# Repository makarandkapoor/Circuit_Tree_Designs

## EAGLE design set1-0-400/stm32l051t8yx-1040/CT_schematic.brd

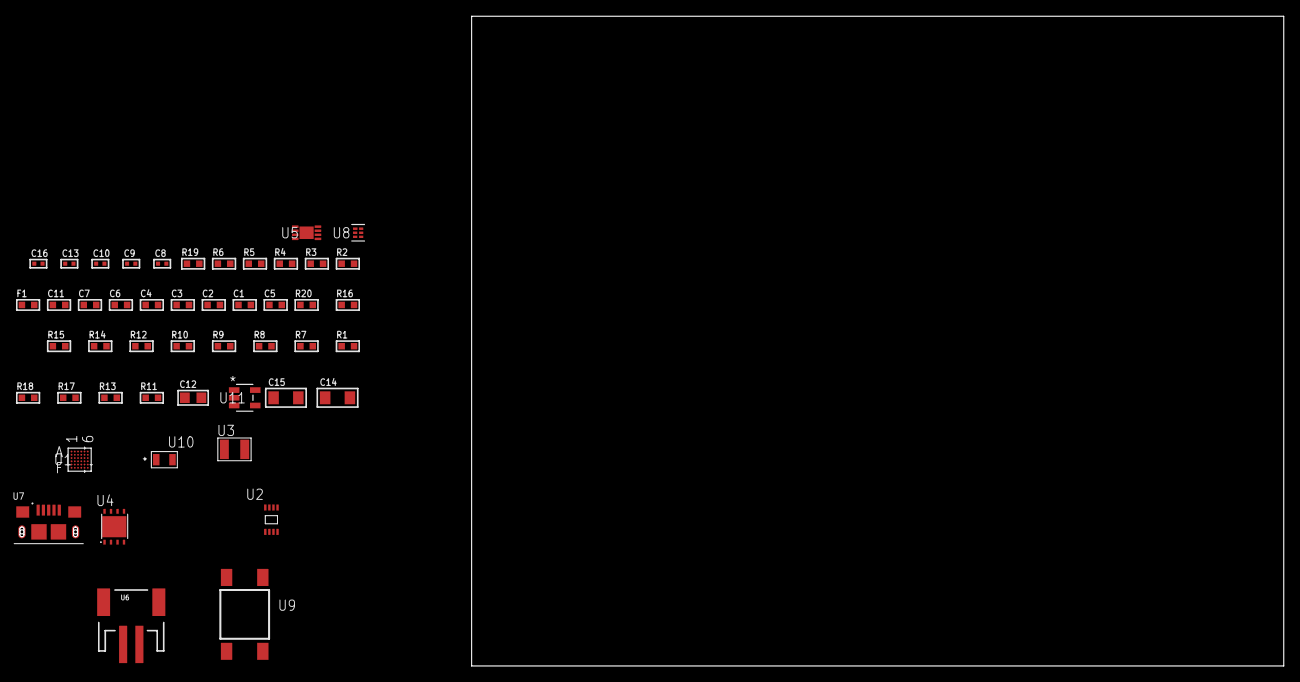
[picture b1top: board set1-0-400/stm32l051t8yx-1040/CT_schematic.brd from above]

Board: 2 copper layers, 155.6 x 80.0 mm, 48 parts (0 on the bottom side), 24 nets, no tracks yet.

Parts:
C1, C2, C3, C4: 1e-07; C0603
C5: 4.7e-06; C0603
C6: 1e-08; C0603
C7, C11: 1e-06; C0603
C8, C9: 1e-11; C0402
C10, C16: 1e-08; C0402
C12: 1e-05; C0805
C13: 1e-07; C0402
C14, C15: 1e-05; C1206
F1: 240.0; L0603
R1, R7, R8, R9, R10, R14, R15, R20: 10000.0; R0603
R2: 1000.0; R0603
R3: 910.0; R0603
R4: 4700.0; R0603
R5, R6: 2200.0; R0603
R11, R13: 100000.0; R0603
R12: 36000.0; R0603
R16: 82000.0; R0603
R17: 300000.0; R0603
R18: 120000.0; R0603
R19: 2000.0; R0603
U1: STM32L051T8Y6; WLCSP36
U2: 24AA32AT-I/MNY; TDFN-8/6MM
U3: ABS07-32.768KHZ-7-T
U4: LP2951ACSDX/NOPB; WSON-8
U5: MCP73831T-2ACI/MC; DFN8_2X3MC
U6: S2B-PH-SM4-TB(LF)(SN); JST-2-SMD
U7: 10118193-0001LF; FCI_10118193-0001LF
U8: TPS3895ADRYR; SON-6
U9: 4-1437565-2; SW_4-1437565-2
U10: Q65110A2395; LGM67K-G1J2-24-Z
U11: nc7sz125m5x; NC7SZ125M5X

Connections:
CLK_CRYSTAL_U1_A6: C8.1, U1.A6, U3.1
CLK_CRYSTAL_U1_B6: C9.1, U1.B6, U3.2
GND: C1.2, C2.2, C3.2, C4.2, C5.2, C6.2, C7.2, C8.2, C9.2, C10.2, C11.2, C12.2, C13.2, C14.2, C15.2, C16.2, R2.2, R7.2, R10.2, R13.2, R16.2, R18.2, R19.2, U1.D6, U2.4, U2.7, U4.3, U4.4, U4.PAD, U5.6, U5.9, U6.2, U7.5, U7.6, U7.7, U7.8, U7.9, U8.2, U10.C, U11.1, U11.3
INPUT_USBPOWER_5V: C14.1, R20.2, U5.1, U5.2, U7.1
NET_U1_A4: R6.1, U1.A4, U2.5
NET_U1_B4: R5.1, U1.B4, U2.6
NET_U1_C5: R7.1, U1.C5
NET_U1_C6: R4.1, U1.C6, U11.4
NET_U1_D5: C6.1, C7.1, F1.1, U1.D5, U1.E6
NET_U1_F5: R3.1, U1.F5, U10.A
NET_U1_F6: R1.1, U1.F6, U9.3, U9.4
NET_U2_1: R8.1, U2.1
NET_U2_2: R9.1, U2.2
NET_U2_3: R10.1, U2.3
NET_U4_5: R11.1, U4.5
NET_U4_7: R12.2, R13.1, U4.7
NET_U5_5: R20.1, U5.5
NET_U5_8: R19.1, U5.8
NET_U8_1: R15.1, R16.1, U8.1
NET_U8_3: R17.2, R18.1, U8.3
NET_U8_4: R14.1, U8.4, U11.2
NET_U9_1: R2.1, U9.1, U9.2
VCC_S1_3V7: C11.1, C15.1, U4.8, U5.3, U5.4, U6.1
VCC_TIER1_1V8: C1.1, C2.1, C3.1, C4.1, C5.1, C10.1, C12.1, C13.1, C16.1, F1.2, R1.2, R3.2, R4.2, R5.2, R6.2, R8.2, R9.2, R11.2, R12.1, R14.2, R15.2, R17.1, U1.A5, U1.F1, U2.8, U4.1, U8.6, U11.5

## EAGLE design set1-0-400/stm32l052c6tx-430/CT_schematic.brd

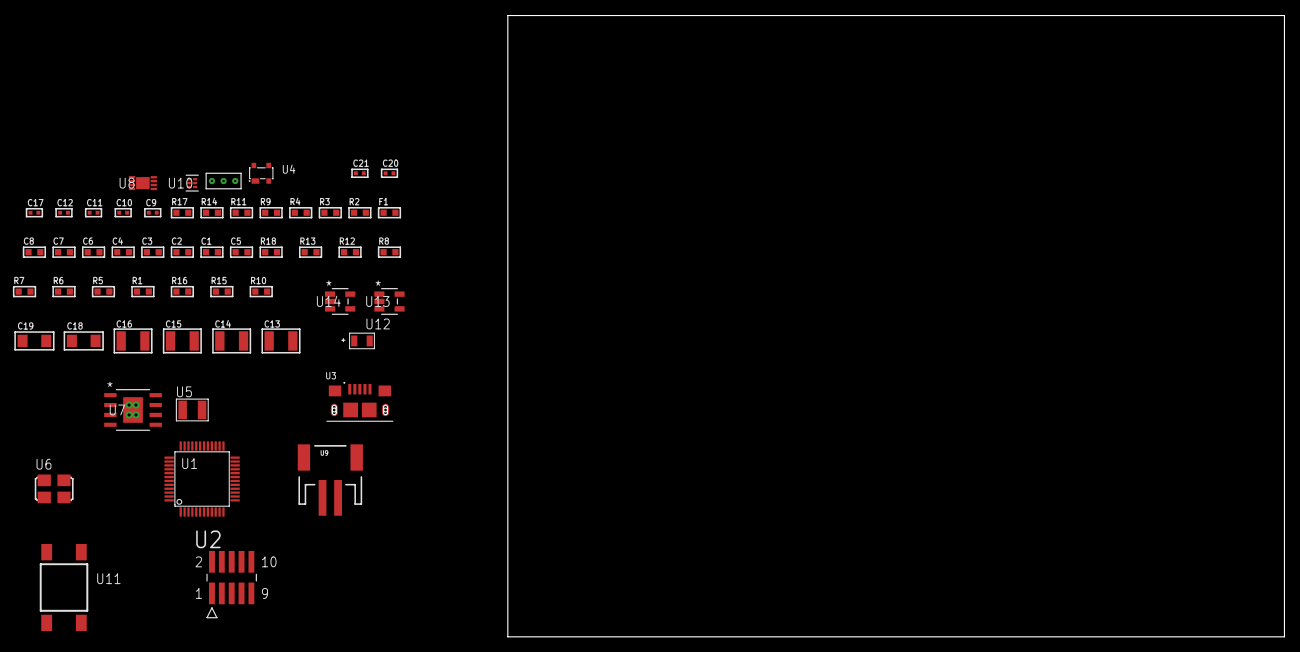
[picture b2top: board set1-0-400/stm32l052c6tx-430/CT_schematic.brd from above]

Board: 2 copper layers, 122.6 x 80.0 mm, 55 parts (0 on the bottom side), 27 nets, no tracks yet.

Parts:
C1, C2, C3, C4, C8: 1e-07; C0603
C5: 4.7e-06; C0603
C6: 1e-08; C0603
C7: 1e-06; C0603
C9, C10: 1e-11; C0402
C11, C17: 1e-07; C0402
C12, C20, C21: 1e-08; C0402
C13, C14, C15, C16: 1e-05; C1210
C18, C19: 1e-05; C1206
F1: 240.0; L0603
R1, R5, R6, R7, R8, R12, R13, R18: 10000.0; R0603
R2: 1000.0; R0603
R3: 1600.5; R0603
R4: 4700.0; R0603
R9: 5.0; R0603
R10: 4031.5447154472; R0603
R11: 2200.0; R0603
R14: 9100.0; R0603
R15: 680000.0; R0603
R16: 120000.0; R0603
R17: 2000.0; R0603
U1: STM32L052C6T6; LQFP48
U2: FTSH-105-01-L-DV-K; SAMTEC_FTSH-105-01-L-DV-K
U3: 10118193-0001LF; FCI_10118193-0001LF
U4: prtr5v0u2ax; SOT143B
U5: ABS07-32.768KHZ-7-T
U6: ASFL1-25MHZ-NCS; ASFL1
U7: MIC5234YME; SOIC-8_EP
U8: MCP73831T-2ACI/MC; DFN8_2X3MC
U9: S2B-PH-SM4-TB(LF)(SN); JST-2-SMD
U10: TPS3895ADRYR; SON-6
U11: 4-1437565-2; SW_4-1437565-2
U12: Q65110A2395; LGM67K-G1J2-24-Z
U13, U14: nc7sz125m5x; NC7SZ125M5X
U15: Dummy; DUMMY_PACKAGE_116

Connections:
CLK_CRYSTAL_U1_3: C9.1, U1.3, U5.1
CLK_CRYSTAL_U1_4: C10.1, U1.4, U5.2
CLK_U1_5: U1.5, U6.3
GND: C1.2, C2.2, C3.2, C4.2, C5.2, C6.2, C7.2, C8.2, C9.2, C10.2, C11.2, C12.2, C13.2, C14.2, C15.2, C16.2, C17.2, C18.2, C19.2, C20.2, C21.2, R2.2, R5.2, R9.2, R11.2, R14.2, R16.2, R17.2, U1.8, U1.23, U1.35, U1.47, U2.3, U2.5, U3.5, U3.6, U3.7, U3.8, U3.9, U4.1, U6.2, U7.7, U7.EPAD, U8.6, U8.9, U9.2, U10.2, U12.C, U13.2, U13.3, U14.1, U14.3, U15.1
INPUT_USBPOWER_5V: C18.1, R18.2, U3.1, U4.4, U8.1, U8.2
NET_U1_7: R4.1, U1.7, U14.4
NET_U1_9: C6.1, C7.1, F1.1, U1.9
NET_U1_44: R5.1, U1.44
NET_U1_45: R3.1, U1.45, U12.A
NET_U1_46: R1.1, U1.46, U11.3, U11.4
NET_U2_9: R9.1, U2.9
NET_U7_4: R10.2, R11.1, U7.4
NET_U8_5: R18.1, U8.5
NET_U8_8: R17.1, U8.8
NET_U10_1: R13.1, R14.1, U10.1
NET_U10_3: R15.2, R16.1, U10.3
NET_U10_4: R12.1, U10.4, U13.4, U14.2
NET_U11_1: R2.1, U11.1, U11.2
PROC_SYS_SWCLK: R7.1, U1.37, U2.4
PROC_SYS_SWDIO: R8.1, U1.34, U2.2
PROC_TIM2_CH1: U1.10, U15.3
PROC_TIM2_CH3: U1.12, U15.2
PROC_USB_DM: U1.32, U3.2, U4.3
PROC_USB_DP: U1.33, U3.3, U4.2
RST_OUT_U2_JTAG_RST_B: R6.1, U2.10, U13.1
VCC_S1_3V7: C13.1, C14.1, C19.1, U7.5, U7.8, U8.3, U8.4, U9.1
VCC_TIER1_3V3: C1.1, C2.1, C3.1, C4.1, C5.1, C8.1, C11.1, C12.1, C15.1, C16.1, C17.1, C20.1, C21.1, F1.2, R1.2, R3.2, R4.2, R6.2, R7.2, R8.2, R10.1, R12.2, R13.2, R15.1, U1.1, U1.24, U1.36, U1.48, U2.1, U6.4, U7.1, U10.6, U13.5, U14.5

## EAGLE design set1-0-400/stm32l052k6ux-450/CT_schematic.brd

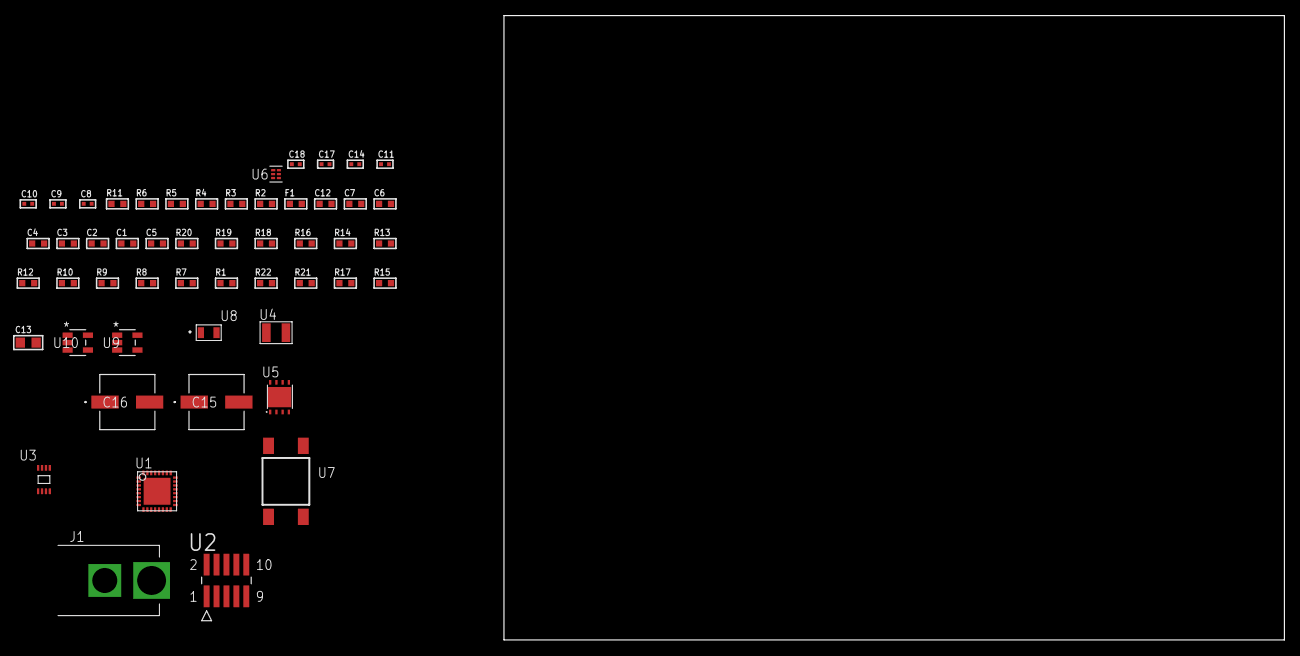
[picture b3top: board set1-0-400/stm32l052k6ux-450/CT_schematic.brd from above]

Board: 2 copper layers, 100.0 x 80.0 mm, 52 parts (0 on the bottom side), 25 nets, no tracks yet.

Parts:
C1, C2, C3, C4: 1e-07; C0603
C5: 4.7e-06; C0603
C6: 1e-08; C0603
C7, C12: 1e-06; C0603
C8, C9: 1e-11; C0402
C10, C14: 1e-07; C0402
C11, C17, C18: 1e-08; C0402
C13: 1e-05; C0805
C15, C16: 0.0001; EXV-9H
F1: 240.0; L0603
J1: PJ-037B; PJ-037B_PACKAGE
R1, R7, R8, R9, R10, R12, R13, R14, R18, R19: 10000.0; R0603
R2: 1000.0; R0603
R3: 910.0; R0603
R4: 4700.0; R0603
R5, R6: 2200.0; R0603
R11: 5.0; R0603
R15, R17: 100000.0; R0603
R16: 36000.0; R0603
R20: 82000.0; R0603
R21: 300000.0; R0603
R22: 120000.0; R0603
U1: STM32L052K6U6; UFQFPN32
U2: FTSH-105-01-L-DV-K; SAMTEC_FTSH-105-01-L-DV-K
U3: 24AA128T-I/MNY; TDFN-8/6MM
U4: ABS07-32.768KHZ-7-T
U5: LP2951ACSDX/NOPB; WSON-8
U6: TPS3895ADRYR; SON-6
U7: 4-1437565-2; SW_4-1437565-2
U8: Q65110A2395; LGM67K-G1J2-24-Z
U9, U10: nc7sz125m5x; NC7SZ125M5X

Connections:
CLK_CRYSTAL_U1_2: C8.1, U1.2, U4.1
CLK_CRYSTAL_U1_3: C9.1, U1.3, U4.2
GND: C1.2, C2.2, C3.2, C4.2, C5.2, C6.2, C7.2, C8.2, C9.2, C10.2, C11.2, C12.2, C13.2, C14.2, C15.2, C16.2, C17.2, C18.2, J1.2, R2.2, R7.2, R11.2, R12.2, R14.2, R17.2, R20.2, R22.2, U1.EPAD, U2.3, U2.5, U3.4, U5.3, U5.4, U5.PAD, U6.2, U8.C, U9.2, U9.3, U10.1, U10.3
NET_U1_4: R4.1, U1.4, U10.4
NET_U1_5: C6.1, C7.1, F1.1, U1.5
NET_U1_28: R3.1, U1.28, U8.A
NET_U1_29: R5.1, U1.29, U3.6
NET_U1_30: R6.1, U1.30, U3.5
NET_U1_31: R7.1, U1.31
NET_U1_32: R1.1, U1.32, U7.3, U7.4
NET_U2_9: R11.1, U2.9
NET_U3_1: R12.1, U3.1
NET_U3_2: R13.1, U3.2
NET_U3_3: R14.1, U3.3
NET_U5_5: R15.1, U5.5
NET_U5_7: R16.2, R17.1, U5.7
NET_U6_1: R19.1, R20.1, U6.1
NET_U6_3: R21.2, R22.1, U6.3
NET_U6_4: R18.1, U6.4, U9.4, U10.2
NET_U7_1: R2.1, U7.1, U7.2
PROC_SYS_SWCLK: R9.1, U1.24, U2.4
PROC_SYS_SWDIO: R10.1, U1.23, U2.2
RST_OUT_U2_JTAG_RST_B: R8.1, U2.10, U9.1
VCC_S1_9V8: C12.1, C15.1, C16.1, J1.1, U5.8
VCC_TIER1_1V8: C1.1, C2.1, C3.1, C4.1, C5.1, C10.1, C11.1, C13.1, C14.1, C17.1, C18.1, F1.2, R1.2, R3.2, R4.2, R5.2, R6.2, R8.2, R9.2, R10.2, R13.2, R15.2, R16.1, R18.2, R19.2, R21.1, U1.1, U1.17, U2.1, U3.7, U3.8, U5.1, U6.6, U9.5, U10.5

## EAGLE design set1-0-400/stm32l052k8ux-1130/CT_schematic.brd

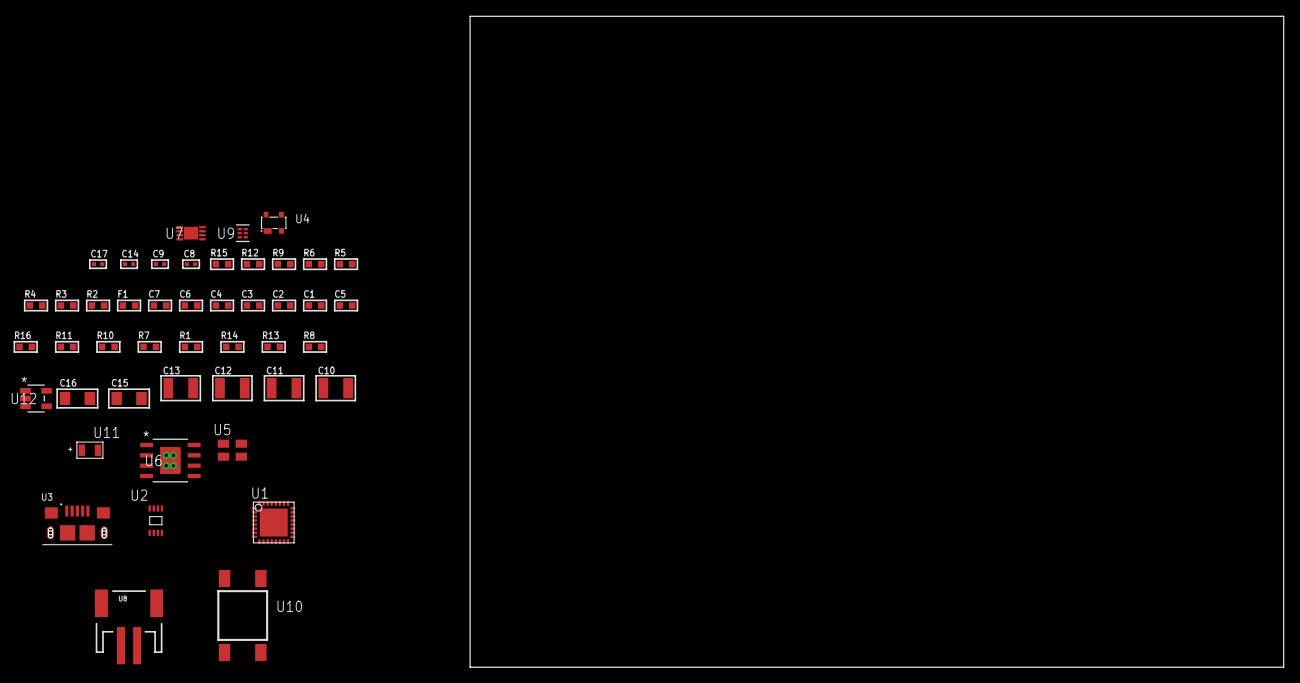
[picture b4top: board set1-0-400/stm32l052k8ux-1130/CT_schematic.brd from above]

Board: 2 copper layers, 151.8 x 80.0 mm, 46 parts (0 on the bottom side), 21 nets, no tracks yet.

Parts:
C1, C2, C3, C4: 1e-07; C0603
C5: 4.7e-06; C0603
C6: 1e-08; C0603
C7: 1e-06; C0603
C8, C9, C17: 1e-08; C0402
C10, C11, C12, C13: 1e-05; C1210
C14: 1e-07; C0402
C15, C16: 1e-05; C1206
F1: 240.0; L0603
R1, R7, R10, R11, R16: 10000.0; R0603
R2: 1000.0; R0603
R3: 1600.5; R0603
R4: 4700.0; R0603
R5, R6, R9: 2200.0; R0603
R8: 4031.5447154472; R0603
R12: 9100.0; R0603
R13: 680000.0; R0603
R14: 120000.0; R0603
R15: 2000.0; R0603
U1: STM32L052K8U6; UFQFPN32
U2: 24AA00T-I/MNY; TDFN-8/6MM
U3: 10118193-0001LF; FCI_10118193-0001LF
U4: prtr5v0u2ax; SOT143B
U5: ASEK-32.768KHz-ECST; ASEK
U6: MIC5234YME; SOIC-8_EP
U7: MCP73831T-2ACI/MC; DFN8_2X3MC
U8: S2B-PH-SM4-TB(LF)(SN); JST-2-SMD
U9: TPS3895ADRYR; SON-6
U10: 4-1437565-2; SW_4-1437565-2
U11: Q65110A2395; LGM67K-G1J2-24-Z
U12: nc7sz125m5x; NC7SZ125M5X

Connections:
CLK_U1_2: U1.2, U5.3
GND: C1.2, C2.2, C3.2, C4.2, C5.2, C6.2, C7.2, C8.2, C9.2, C10.2, C11.2, C12.2, C13.2, C14.2, C15.2, C16.2, C17.2, R2.2, R7.2, R9.2, R12.2, R14.2, R15.2, U1.EPAD, U2.4, U3.5, U3.6, U3.7, U3.8, U3.9, U4.1, U5.2, U6.7, U6.EPAD, U7.6, U7.9, U8.2, U9.2, U11.C, U12.1, U12.3
INPUT_USBPOWER_5V: C15.1, R16.2, U3.1, U4.4, U7.1, U7.2
NET_U1_4: R4.1, U1.4, U12.4
NET_U1_5: C6.1, C7.1, F1.1, U1.5
NET_U1_28: R3.1, U1.28, U11.A
NET_U1_29: R5.1, U1.29, U2.6
NET_U1_30: R6.1, U1.30, U2.5
NET_U1_31: R7.1, U1.31
NET_U1_32: R1.1, U1.32, U10.3, U10.4
NET_U6_4: R8.2, R9.1, U6.4
NET_U7_5: R16.1, U7.5
NET_U7_8: R15.1, U7.8
NET_U9_1: R11.1, R12.1, U9.1
NET_U9_3: R13.2, R14.1, U9.3
NET_U9_4: R10.1, U9.4, U12.2
NET_U10_1: R2.1, U10.1, U10.2
PROC_USB_DM: U1.21, U3.2, U4.3
PROC_USB_DP: U1.22, U3.3, U4.2
VCC_S1_3V7: C10.1, C11.1, C16.1, U6.5, U6.8, U7.3, U7.4, U8.1
VCC_TIER1_3V3: C1.1, C2.1, C3.1, C4.1, C5.1, C8.1, C9.1, C12.1, C13.1, C14.1, C17.1, F1.2, R1.2, R3.2, R4.2, R5.2, R6.2, R8.1, R10.2, R11.2, R13.1, U1.1, U1.17, U2.8, U5.4, U6.1, U9.6, U12.5

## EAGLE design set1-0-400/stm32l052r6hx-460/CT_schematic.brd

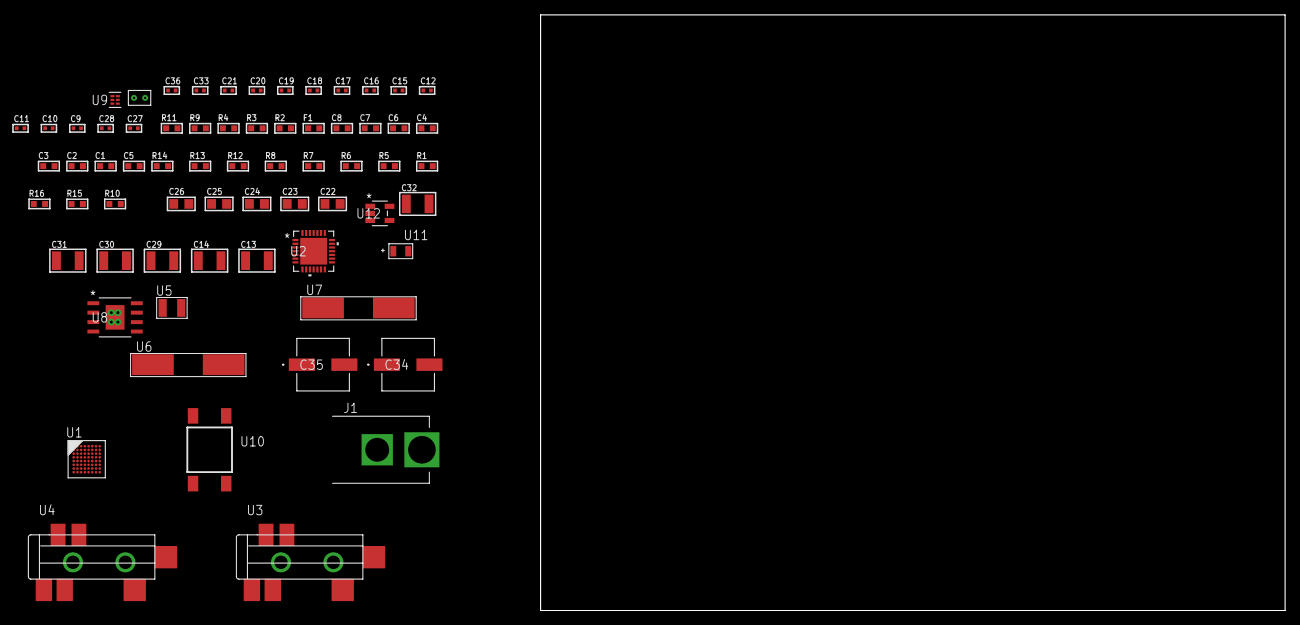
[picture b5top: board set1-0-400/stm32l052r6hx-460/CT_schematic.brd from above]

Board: 2 copper layers, 100.0 x 80.0 mm, 67 parts (0 on the bottom side), 27 nets, no tracks yet.

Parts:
C1, C2, C3, C4, C8: 1e-07; C0603
C5: 4.7e-06; C0603
C6: 1e-08; C0603
C7: 1e-06; C0603
C9, C10, C11, C12: 1e-11; C0402
C13, C14: 2.2e-05; C1210
C15, C16: 1e-09; C0402
C17, C18, C19, C20, C21, C33: 1e-07; C0402
C22, C23, C24, C25, C26: 1e-05; C0805
C27, C28: 2.2e-11; C0402
C29, C30, C31, C32: 1e-05; C1210
C34, C35: 0.0001; EXV-9H
C36: 1e-08; C0402
F1: 240.0; L0603
J1: PJ-037B; PJ-037B_PACKAGE
R1, R5, R12, R13: 10000.0; R0603
R2: 1000.0; R0603
R3: 910.0; R0603
R4: 4700.0; R0603
R6, R7, R8: 47000.0; R0603
R9: 680.0; R0603
R10: 1402.2764227642; R0603
R11: 2200.0; R0603
R14: 82000.0; R0603
R15: 300000.0; R0603
R16: 120000.0; R0603
U1: STM32L052R6H6; TFBGA64
U2: WM8731CLSEFL; QFN-28
U3, U4: SJ-43515TS-SMT-TR
U5: ABS07-32.768KHZ-7-T
U6: ABLS-25.000MHZ-B2F-T
U7: ABLS-12.288MHZ-B4-T
U8: MIC5234YME; SOIC-8_EP
U9: TPS3895ADRYR; SON-6
U10: 4-1437565-2; SW_4-1437565-2
U11: Q65110A2395; LGM67K-G1J2-24-Z
U12: nc7sz125m5x; NC7SZ125M5X
U13: Dummy; DUMMY_PACKAGE_132

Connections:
CLK_CRYSTAL_U1_A1: C9.1, U1.A1, U5.1
CLK_CRYSTAL_U1_B1: C10.1, U1.B1, U5.2
CLK_CRYSTAL_U1_C1: C11.1, U1.C1, U6.1
CLK_CRYSTAL_U1_D1: C12.1, U1.D1, U6.2
CLK_CRYSTAL_U2_1: C27.1, U2.1, U7.1
CLK_CRYSTAL_U2_2: C28.1, U2.2, U7.2
GND: C1.2, C2.2, C3.2, C4.2, C5.2, C6.2, C7.2, C8.2, C9.2, C10.2, C11.2, C12.2, C16.2, C17.2, C18.2, C19.2, C20.2, C21.2, C22.2, C23.2, C24.2, C25.2, C26.2, C27.2, C28.2, C29.2, C30.2, C31.2, C32.2, C33.2, C34.2, C35.2, C36.2, J1.2, R2.2, R5.2, R6.2, R7.2, R8.2, R11.2, R14.2, R16.2, U1.C2, U1.D4, U1.D5, U1.D6, U1.F1, U2.4, U2.15, U2.19, U2.25, U2.26, U2.29, U3.1, U4.1, U8.7, U8.EPAD, U9.2, U11.C, U12.1, U12.3, U13.1
NET_U1_B4: R5.1, U1.B4
NET_U1_E1: R4.1, U1.E1, U12.4
NET_U1_H1: C6.1, C7.1, F1.1, U1.G1, U1.H1
NET_U1_H7: R3.1, U1.H7, U11.A
NET_U1_H8: R1.1, U1.H8, U10.3, U10.4
NET_U2_20: C21.1, C26.1, U2.20
NET_U3_2: C14.1, R7.1, U3.2
NET_U3_5: C13.1, R6.1, U3.5
NET_U4_5: C15.1, C16.1, R8.1, R9.1, U4.5
NET_U8_4: R10.2, R11.1, U8.4
NET_U9_1: R13.1, R14.1, U9.1
NET_U9_3: R15.2, R16.1, U9.3
NET_U9_4: R12.1, U9.4, U12.2
NET_U10_1: R2.1, U10.1, U10.2
PROC_DAC_OUT1: U1.H3, U13.2
PROC_I2S2_CK: U1.G8, U2.7
PROC_I2S2_SD: U1.F7, U2.8
PROC_I2S2_WS: U1.A3, U2.9, U2.11
VCC_S1_11V3: C29.1, C30.1, C34.1, C35.1, J1.1, U8.5, U8.8
VCC_TIER1_1V8: C1.1, C2.1, C3.1, C4.1, C5.1, C8.1, C17.1, C18.1, C19.1, C20.1, C22.1, C23.1, C24.1, C25.1, C31.1, C32.1, C33.1, C36.1, F1.2, R1.2, R3.2, R4.2, R10.1, R12.2, R13.2, R15.1, U1.B2, U1.D2, U1.E4, U1.E5, U1.E6, U2.3, U2.5, U2.12, U2.18, U8.1, U9.6, U12.5

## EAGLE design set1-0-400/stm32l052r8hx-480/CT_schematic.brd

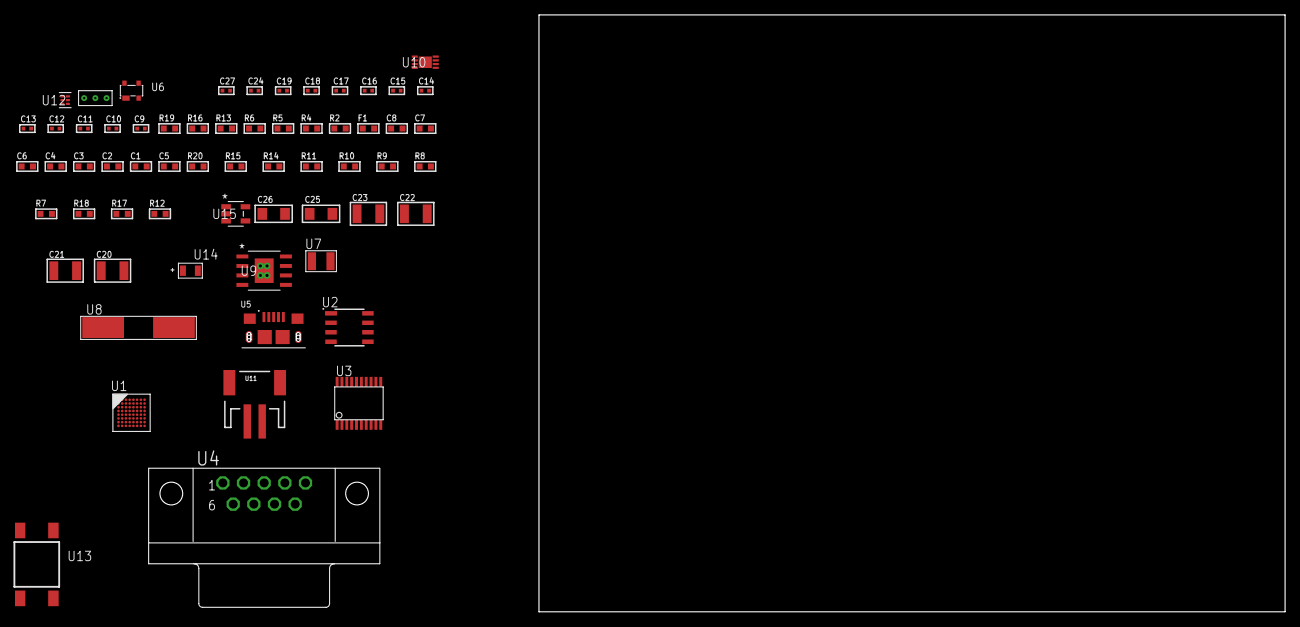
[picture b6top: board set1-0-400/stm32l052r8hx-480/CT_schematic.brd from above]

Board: 2 copper layers, 62 parts (0 on the bottom side), 43 nets, no tracks yet.

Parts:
C1, C2, C3, C4, C8: 1e-07; C0603
C5: 4.7e-06; C0603
C6: 1e-08; C0603
C7: 1e-06; C0603
C9, C10, C11, C12: 1e-11; C0402
C13, C27: 1e-08; C0402
C14, C15, C16, C17, C18, C19, C24: 1e-07; C0402
C20, C21, C22, C23: 1e-05; C1210
C25, C26: 1e-05; C1206
F1: 240.0; L0603
R2: 1000.0; R0603
R4: 4700.0; R0603
R5, R6, R13: 2200.0; R0603
R7, R8, R9, R10, R11, R14, R15, R20: 10000.0; R0603
R12: 4031.5447154472; R0603
R16: 9100.0; R0603
R17: 680000.0; R0603
R18: 120000.0; R0603
R19: 2000.0; R0603
U1: STM32L052R8H6; TFBGA64
U2: AT24C02D-SSHM-T; AT24C02D
U3: SP3203ECY-L/TR; TSSOP20-I
U4: 182-009-113R531; 182-009-MALE
U5: 10118193-0001LF; FCI_10118193-0001LF
U6: prtr5v0u2ax; SOT143B
U7: ABS07-32.768KHZ-7-T
U8: ABLS-25.000MHZ-B2F-T
U9: MIC5234YME; SOIC-8_EP
U10: MCP73831T-2ACI/MC; DFN8_2X3MC
U11: S2B-PH-SM4-TB(LF)(SN); JST-2-SMD
U12: TPS3895ADRYR; SON-6
U13: 4-1437565-2; SW_4-1437565-2
U14: Q65110A2395; LGM67K-G1J2-24-Z
U15: nc7sz125m5x; NC7SZ125M5X
U16: Dummy; DUMMY_PACKAGE_132

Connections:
CLK_CRYSTAL_U1_A1: C9.1, U1.A1, U7.1
CLK_CRYSTAL_U1_B1: C10.1, U1.B1, U7.2
CLK_CRYSTAL_U1_C1: C11.1, U1.C1, U8.1
CLK_CRYSTAL_U1_D1: C12.1, U1.D1, U8.2
GND: C1.2, C2.2, C3.2, C4.2, C5.2, C6.2, C7.2, C8.2, C9.2, C10.2, C11.2, C12.2, C13.2, C14.2, C15.2, C18.2, C19.2, C20.2, C21.2, C22.2, C23.2, C24.2, C25.2, C26.2, C27.2, R2.2, R7.2, R8.2, R10.2, R11.2, R13.2, R16.2, R18.2, R19.2, U1.C2, U1.D4, U1.D5, U1.D6, U1.F1, U2.4, U3.18, U4.5, U5.5, U5.6, U5.7, U5.8, U5.9, U6.1, U9.7, U9.EPAD, U10.6, U10.9, U11.2, U12.2, U14.C, U15.1, U15.3, U16.1
INPUT_USBPOWER_5V: C25.1, R20.2, U5.1, U6.4, U10.1, U10.2
NET_U1_A3: R6.1, U1.A3, U2.5
NET_U1_B3: R5.1, U1.B3, U2.6
NET_U1_B4: R7.1, U1.B4
NET_U1_E1: R4.1, U1.E1, U15.4
NET_U1_H1: C6.1, C7.1, F1.1, U1.G1, U1.H1
NET_U1_H8: U13.3, U13.4
NET_U2_1: R9.1, U2.1
NET_U2_2: R10.1, U2.2
NET_U2_3: R11.1, U2.3
NET_U2_7: R8.1, U2.7
NET_U3_1: C16.1, U3.1
NET_U3_2: C18.1, U3.2
NET_U3_3: C16.2, U3.3
NET_U3_4: C17.1, U3.4
NET_U3_5: C17.2, U3.5
NET_U3_6: C19.1, U3.6
NET_U4_2: U3.14, U4.2
NET_U4_3: U3.17, U4.3
NET_U4_7: U3.13, U4.7
NET_U4_8: U3.16, U4.8
NET_U9_4: R12.2, R13.1, U9.4
NET_U10_5: R20.1, U10.5
NET_U10_8: R19.1, U10.8
NET_U12_1: R15.1, R16.1, U12.1
NET_U12_3: R17.2, R18.1, U12.3
NET_U12_4: R14.1, U12.4, U15.2
NET_U13_1: R2.1, U13.1, U13.2
PROC_LPUART1_CTS: U1.G4, U3.8
PROC_LPUART1_RTS: U1.B5, U3.10
PROC_LPUART1_RX: U1.B6, U3.11
PROC_LPUART1_TX: U1.B7, U3.7
PROC_TIM2_CH1: U1.A6, U16.3
PROC_TIM2_CH3: U1.F3, U16.2
PROC_USB_DM: U1.C8, U5.2, U6.3
PROC_USB_DP: U1.B8, U5.3, U6.2
VCC_S1_3V7: C20.1, C21.1, C26.1, U9.5, U9.8, U10.3, U10.4, U11.1
VCC_TIER1_3V3: C1.1, C2.1, C3.1, C4.1, C5.1, C8.1, C13.1, C14.1, C15.1, C22.1, C23.1, C24.1, C27.1, F1.2, R4.2, R5.2, R6.2, R9.2, R12.1, R14.2, R15.2, R17.1, U1.B2, U1.D2, U1.E4, U1.E5, U1.E6, U2.8, U3.12, U3.19, U9.1, U12.6, U15.5

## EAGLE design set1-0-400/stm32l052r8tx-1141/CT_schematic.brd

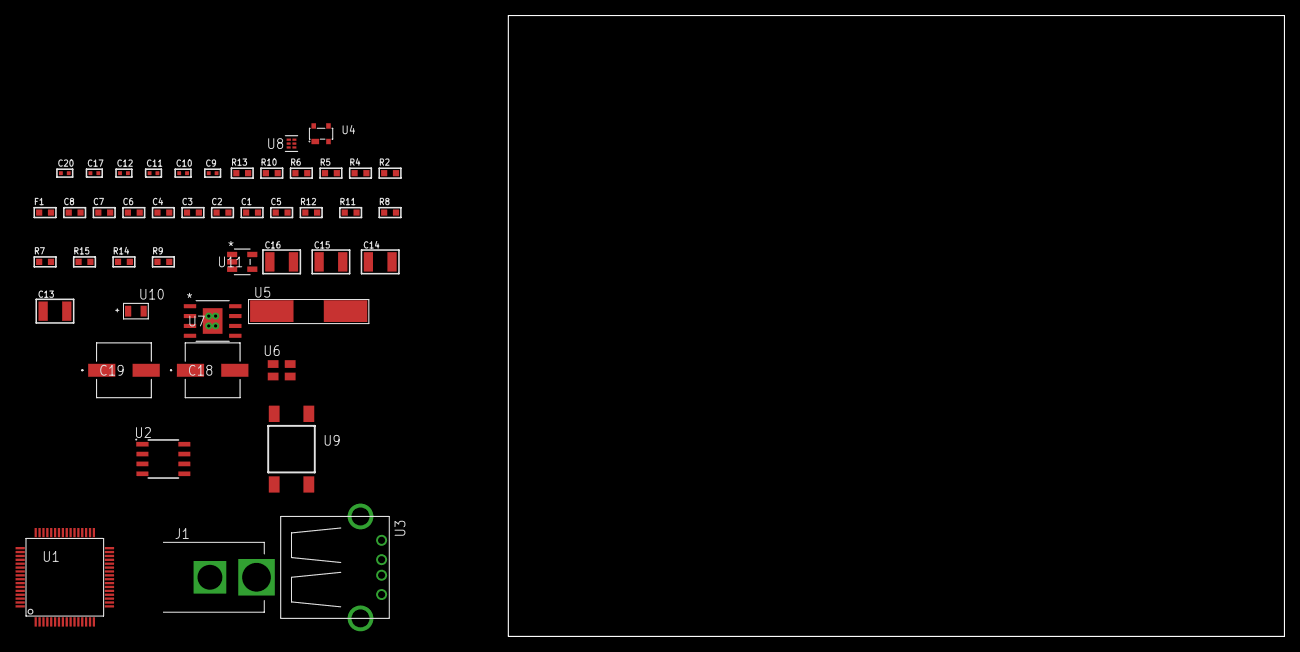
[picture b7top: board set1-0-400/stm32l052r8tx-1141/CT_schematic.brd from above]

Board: 2 copper layers, 100.0 x 80.0 mm, 46 parts (0 on the bottom side), 21 nets, no tracks yet.

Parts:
C1, C2, C3, C4, C8: 1e-07; C0603
C5: 4.7e-06; C0603
C6: 1e-08; C0603
C7: 1e-06; C0603
C9, C10: 1e-11; C0402
C11, C12, C20: 1e-08; C0402
C13, C14, C15, C16: 1e-05; C1210
C17: 1e-07; C0402
C18, C19: 0.0001; EXV-9H
F1: 240.0; L0603
J1: PJ-037B; PJ-037B_PACKAGE
R2: 1000.0; R0603
R4: 4700.0; R0603
R5, R6, R10: 2200.0; R0603
R7, R8, R11, R12: 10000.0; R0603
R9: 4031.5447154472; R0603
R13: 9100.0; R0603
R14: 680000.0; R0603
R15: 120000.0; R0603
U1: STM32L052R8T6; LQFP64
U2: M24M02-DRMN6TP; SOIC-8
U3: 61400416021; USB-A-H
U4: prtr5v0u2ax; SOT143B
U5: ABLS-25.000MHZ-B2F-T
U6: ASEK-32.768KHz-ECST; ASEK
U7: MIC5234YME; SOIC-8_EP
U8: TPS3895ADRYR; SON-6
U9: 4-1437565-2; SW_4-1437565-2
U10: Q65110A2395; LGM67K-G1J2-24-Z
U11: nc7sz125m5x; NC7SZ125M5X

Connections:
CLK_CRYSTAL_U1_5: C9.1, U1.5, U5.1
CLK_CRYSTAL_U1_6: C10.1, U1.6, U5.2
CLK_U1_3: U1.3, U6.3
GND: C1.2, C2.2, C3.2, C4.2, C5.2, C6.2, C7.2, C8.2, C9.2, C10.2, C11.2, C12.2, C13.2, C14.2, C15.2, C16.2, C17.2, C18.2, C19.2, C20.2, J1.2, R2.2, R7.2, R8.2, R10.2, R13.2, R15.2, U1.12, U1.18, U1.31, U1.47, U1.63, U2.4, U3.4, U3.5, U3.6, U4.1, U6.2, U7.7, U7.EPAD, U8.2, U10.C, U11.1, U11.3
NET_U1_7: R4.1, U1.7, U11.4
NET_U1_13: C6.1, C7.1, F1.1, U1.13
NET_U1_58: R5.1, U1.58, U2.6
NET_U1_59: R6.1, U1.59, U2.5
NET_U1_60: R7.1, U1.60
NET_U1_62: U9.3, U9.4
NET_U2_3: R8.1, U2.3
NET_U4_4: U3.1, U4.4
NET_U7_4: R9.2, R10.1, U7.4
NET_U8_1: R12.1, R13.1, U8.1
NET_U8_3: R14.2, R15.1, U8.3
NET_U8_4: R11.1, U8.4, U11.2
NET_U9_1: R2.1, U9.1, U9.2
PROC_USB_DM: U1.44, U3.2, U4.3
PROC_USB_DP: U1.45, U3.3, U4.2
VCC_S1_5V3: C13.1, C14.1, C18.1, C19.1, J1.1, U7.5, U7.8
VCC_TIER1_3V3: C1.1, C2.1, C3.1, C4.1, C5.1, C8.1, C11.1, C12.1, C15.1, C16.1, C17.1, C20.1, F1.2, R4.2, R5.2, R6.2, R9.1, R11.2, R12.2, R14.1, U1.1, U1.19, U1.32, U1.48, U1.64, U2.8, U6.4, U7.1, U8.6, U11.5

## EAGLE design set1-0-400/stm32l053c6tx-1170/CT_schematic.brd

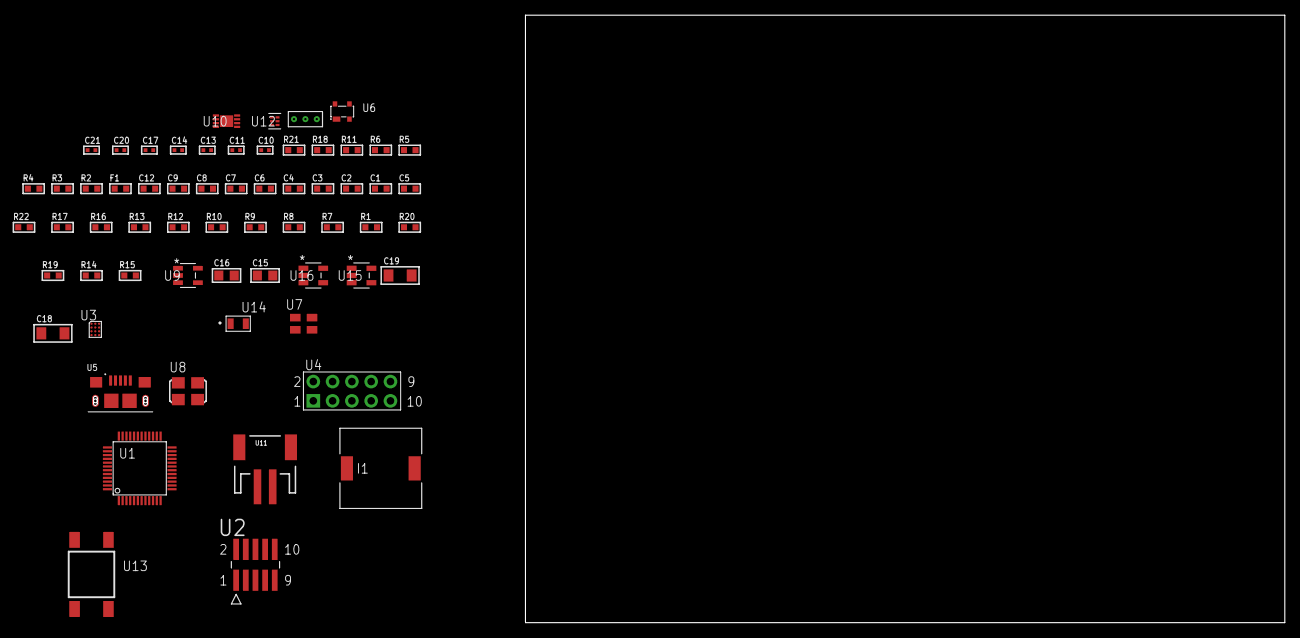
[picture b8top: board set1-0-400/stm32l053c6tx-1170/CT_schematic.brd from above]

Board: 2 copper layers, 156.9 x 80.0 mm, 62 parts (0 on the bottom side), 37 nets, no tracks yet.

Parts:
C1, C2, C3, C4, C6, C9: 1e-07; C0603
C5: 4.7e-06; C0603
C7: 1e-08; C0603
C8, C12: 1e-06; C0603
C10, C11, C17: 1e-07; C0402
C13, C14, C20, C21: 1e-08; C0402
C15, C16: 1e-05; C0805
C18, C19: 1e-05; C1206
F1: 240.0; L0603
I1: 5.2e-06; DR1040
R1, R7, R8, R9, R10, R12, R13, R16, R17, R22: 10000.0; R0603
R2: 1000.0; R0603
R3: 1600.5; R0603
R4: 4700.0; R0603
R5, R6: 2200.0; R0603
R11: 5.0; R0603
R14: 220000.0; R0603
R15: 1000000.0; R0603
R18: 9100.0; R0603
R19: 680000.0; R0603
R20: 120000.0; R0603
R21: 2000.0; R0603
U1: STM32L053C6T7; LQFP48
U2: FTSH-105-01-L-DV-K; SAMTEC_FTSH-105-01-L-DV-K
U3: TSC2014IYZGT
U4: HTSS-105-01-G-D
U5: 10118193-0001LF; FCI_10118193-0001LF
U6: prtr5v0u2ax; SOT143B
U7: ASEK-32.768KHz-ECST; ASEK
U8: ASFL1-25MHZ-NCS; ASFL1
U9: ltc3406es5; TSOT-23-5
U10: MCP73831T-2ACI/MC; DFN8_2X3MC
U11: S2B-PH-SM4-TB(LF)(SN); JST-2-SMD
U12: TPS3895ADRYR; SON-6
U13: 4-1437565-2; SW_4-1437565-2
U14: Q65110A2395; LGM67K-G1J2-24-Z
U15, U16: nc7sz125m5x; NC7SZ125M5X
U17: Dummy; DUMMY_PACKAGE_133

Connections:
CLK_U1_3: U1.3, U7.3
CLK_U1_5: U1.5, U8.3
GND: C1.2, C2.2, C3.2, C4.2, C5.2, C6.2, C7.2, C8.2, C9.2, C10.2, C11.2, C12.2, C13.2, C14.2, C15.2, C16.1, C16.2, C17.2, C18.2, C19.2, C20.2, C21.2, R2.2, R7.2, R11.2, R14.2, R18.2, R20.2, R21.2, U1.8, U1.23, U1.35, U1.47, U2.3, U2.5, U3.B2, U3.D2, U4.9, U5.5, U5.6, U5.7, U5.8, U5.9, U6.1, U7.2, U8.2, U9.2, U10.6, U10.9, U11.2, U12.2, U14.C, U15.2, U15.3, U16.1, U16.3, U17.1
INPUT_USBPOWER_5V: C18.1, R22.2, U5.1, U6.4, U10.1, U10.2
NET_U1_1: C6.1, U1.1
NET_U1_7: R4.1, U1.7, U16.4
NET_U1_9: C7.1, C8.1, F1.1, U1.9
NET_U1_42: R5.1, U1.42, U3.D1
NET_U1_43: R6.1, U1.43, U3.C1
NET_U1_44: R7.1, U1.44
NET_U1_45: R3.1, U1.45, U14.A
NET_U1_46: R1.1, U1.46, U13.3, U13.4
NET_U2_9: R11.1, U2.9
NET_U3_B1: R13.1, U3.B1
NET_U3_C2: R12.1, U3.C2
NET_U4_3: U3.B3, U4.3
NET_U4_4: U3.D3, U4.4
NET_U4_5: U3.A3, U4.5
NET_U4_6: U3.C3, U4.6
NET_U9_3: I1.1, U9.3
NET_U9_5: R14.1, R15.1, U9.5
NET_U9_ATNET_3: I1.2, R15.2
NET_U10_5: R22.1, U10.5
NET_U10_8: R21.1, U10.8
NET_U12_1: R17.1, R18.1, U12.1
NET_U12_3: R19.2, R20.1, U12.3
NET_U12_4: R16.1, U12.4, U15.4, U16.2
NET_U13_1: R2.1, U13.1, U13.2
PROC_SYS_SWCLK: R9.1, U1.37, U2.4
PROC_SYS_SWDIO: R10.1, U1.34, U2.2
PROC_TIM2_CH1: U1.10, U17.3
PROC_TIM2_CH3: U1.12, U17.2
PROC_USB_DM: U1.32, U5.2, U6.3
PROC_USB_DP: U1.33, U5.3, U6.2
RST_OUT_U2_JTAG_RST_B: R8.1, U2.10, U15.1
VCC_S1_3V7: C15.1, C19.1, U9.4, U10.3, U10.4, U11.1
VCC_TIER1_3V3: C1.1, C2.1, C3.1, C4.1, C5.1, C9.1, C10.1, C11.1, C12.1, C13.1, C14.1, C16.2, C17.1, C20.1, C21.1, F1.2, I1.2, R1.2, R3.2, R4.2, R5.2, R6.2, R8.2, R9.2, R10.2, R12.2, R13.2, R15.2, R16.2, R17.2, R19.1, U1.24, U1.36, U1.48, U2.1, U3.A2, U7.4, U8.4, U12.6, U15.5, U16.5
